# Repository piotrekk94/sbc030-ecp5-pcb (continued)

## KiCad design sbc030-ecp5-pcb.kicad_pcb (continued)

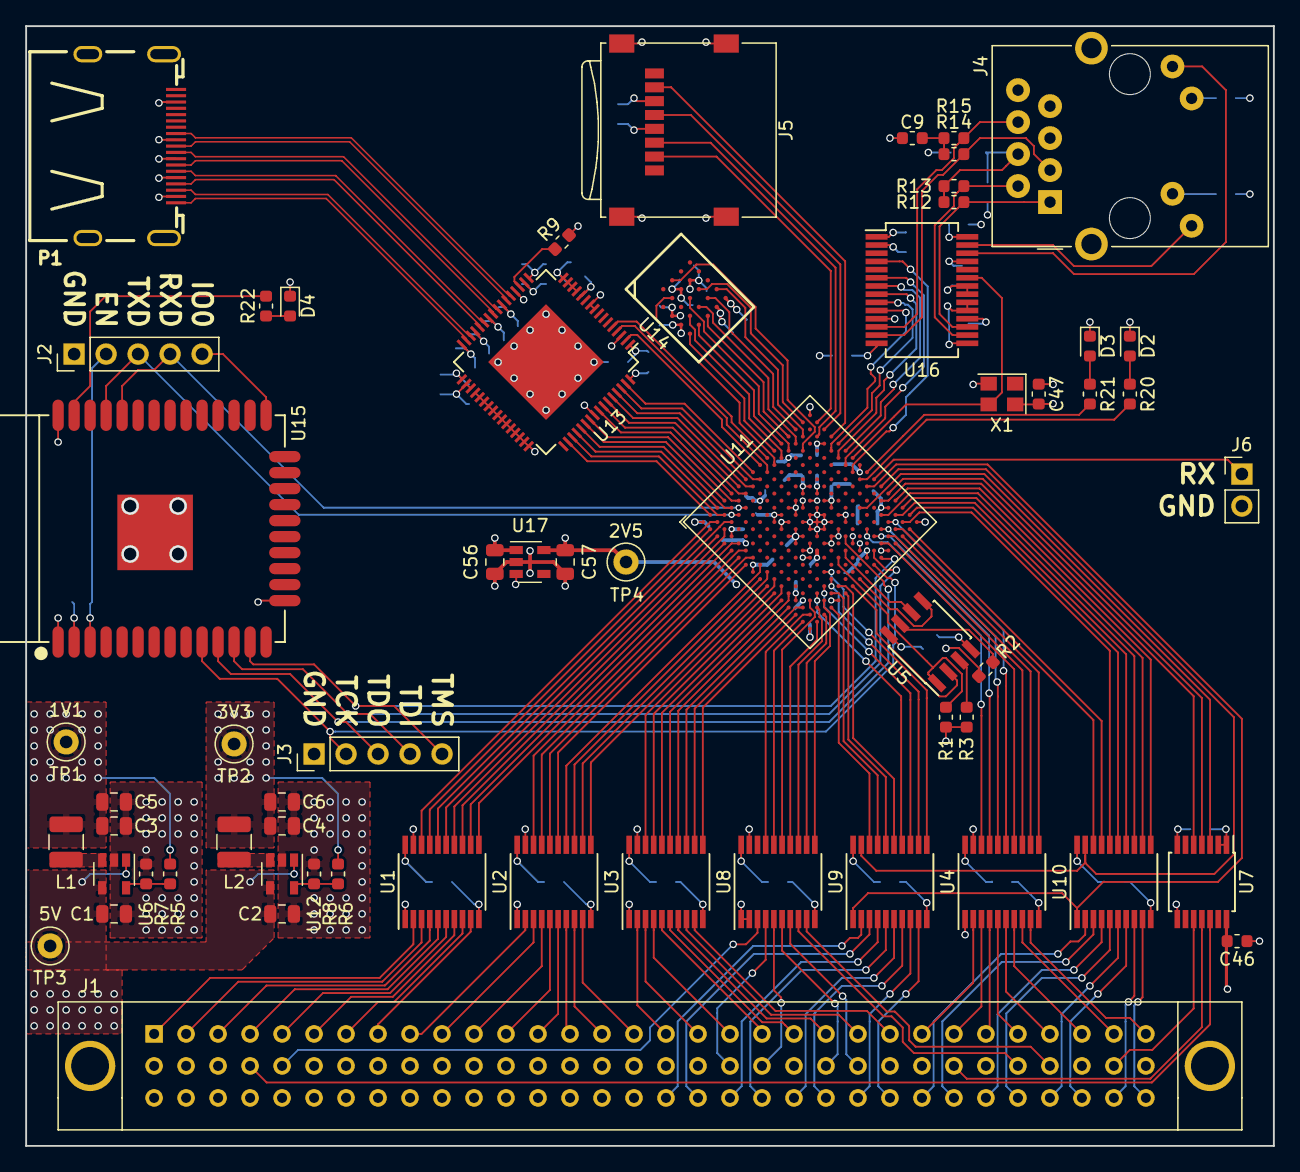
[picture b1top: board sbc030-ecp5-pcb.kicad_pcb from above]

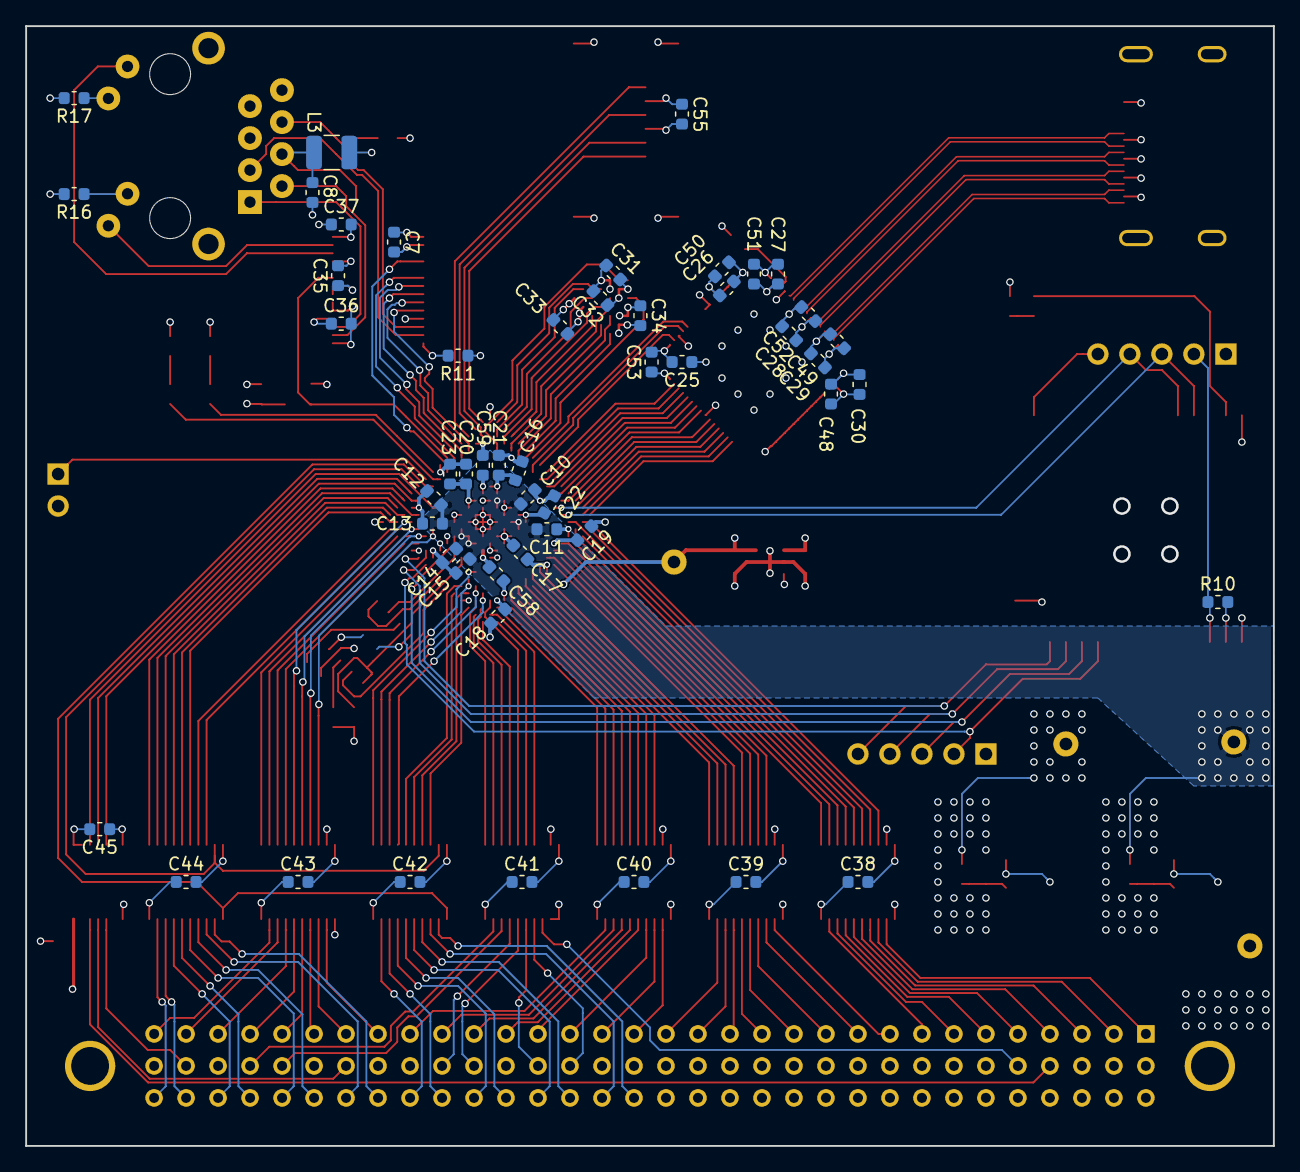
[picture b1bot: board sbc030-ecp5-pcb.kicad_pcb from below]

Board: 4 copper layers, 99.1 x 88.9 mm, 111 parts (51 on the bottom side), 207 nets.
